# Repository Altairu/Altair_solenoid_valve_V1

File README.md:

# Altair_solenoid_valve_V1
Altair_solenoid_valve_V1

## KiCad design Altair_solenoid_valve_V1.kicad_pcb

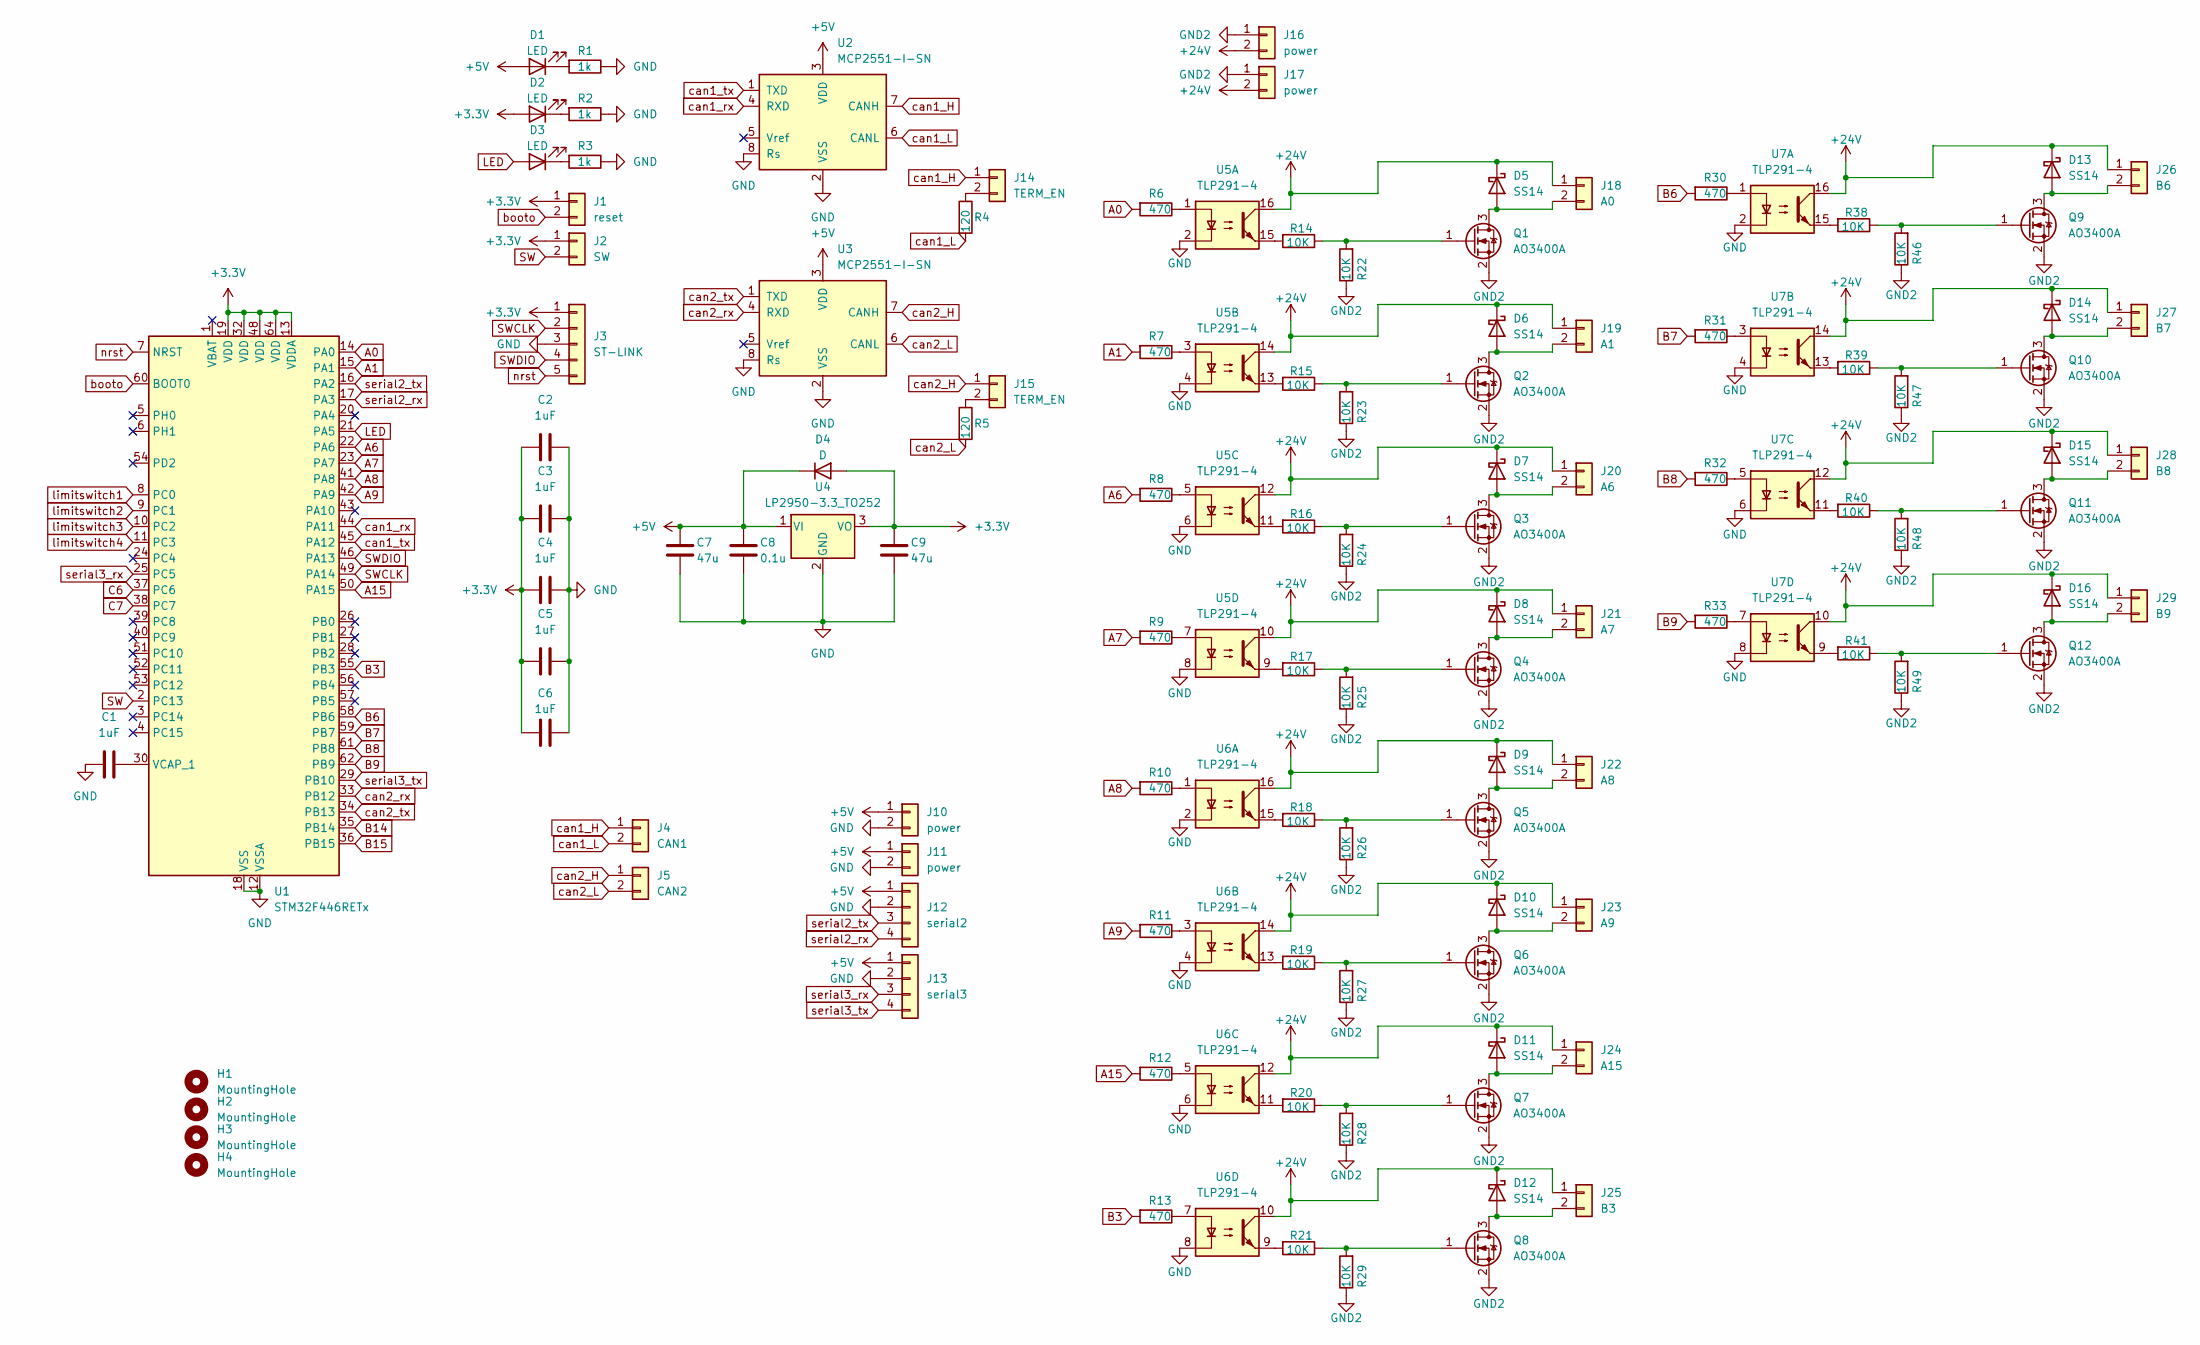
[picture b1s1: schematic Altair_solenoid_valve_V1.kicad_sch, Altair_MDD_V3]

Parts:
C1, C2, C3, C4, C5, C6: 1uF; C_0603_1608Metric
C7, C9: 47u; C_0603_1608Metric
C8: 0.1u; C_0603_1608Metric
D1, D2, D3: LED; LED_0603_1608Metric
D4: D; D_0603_1608Metric
D5, D6, D7, D8, D9, D10, D11, D12, D13, D14, D15, D16: SS14; D_SMA
H1, H2, H3, H4: MountingHole; MountingHole_3.2mm_M3_Pad_Via
J1: reset; PinSocket_1x02_P2.54mm_Vertical
J2: SW; PinSocket_1x02_P2.54mm_Vertical
J3: ST-LINK; PinSocket_1x05_P2.54mm_Vertical
J4: CAN1; JST_XA_S02B-XASK-1_1x02_P2.50mm_Horizontal
J5: CAN2; JST_XA_S02B-XASK-1_1x02_P2.50mm_Horizontal
J10, J11: power; JST_XA_S02B-XASK-1_1x02_P2.50mm_Horizontal
J12: serial2; JST_XA_B04B-XASK-1-A_1x04_P2.50mm_Vertical
J13: serial3; JST_XA_B04B-XASK-1-A_1x04_P2.50mm_Vertical
J14, J15: TERM_EN; PinSocket_1x02_P2.54mm_Vertical
J16, J17: power; AMASS_XT30PW-M_1x02_P2.50mm_Horizontal
J18: A0; AMASS_XT30U-F_1x02_P5.0mm_Vertical
J19: A1; AMASS_XT30U-F_1x02_P5.0mm_Vertical
J20: A6; AMASS_XT30U-F_1x02_P5.0mm_Vertical
J21: A7; AMASS_XT30U-F_1x02_P5.0mm_Vertical
J22: A8; AMASS_XT30U-F_1x02_P5.0mm_Vertical
J23: A9; AMASS_XT30U-F_1x02_P5.0mm_Vertical
J24: A15; AMASS_XT30U-F_1x02_P5.0mm_Vertical
J25: B3; AMASS_XT30U-F_1x02_P5.0mm_Vertical
J26: B6; AMASS_XT30U-F_1x02_P5.0mm_Vertical
J27: B7; AMASS_XT30U-F_1x02_P5.0mm_Vertical
J28: B8; AMASS_XT30U-F_1x02_P5.0mm_Vertical
J29: B9; AMASS_XT30U-F_1x02_P5.0mm_Vertical
Q1, Q2, Q3, Q4, Q5, Q6, Q7, Q8, Q9, Q10, Q11, Q12: AO3400A; SOT-23
R1, R2, R3: 1k; R_0603_1608Metric
R4, R5: 120; R_0603_1608Metric
R6, R7, R8, R9, R10, R11, R12, R13, R30, R31, R32, R33: 470; R_0603_1608Metric
R14, R15, R16, R17, R18, R19, R20, R21, R22, R23, R24, R25, R26, R27, R28, R29, R38, R39, R40, R41, R46, R47, R48, R49: 10K; R_0603_1608Metric
U1: STM32F446RETx; LQFP-64_10x10mm_P0.5mm
U2, U3: MCP2551-I-SN; SOIC-8_3.9x4.9mm_P1.27mm
U4: LP2950-3.3_TO252; TO-252-2
U5, U6, U7: TLP291-4; SOIC-16_4.55x10.3mm_P1.27mm

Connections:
+3.3V: C2.1, C3.1, C4.1, C5.1, C6.1, C9.1, D2.2 (A), D4.2 (A), J1.1, J2.1, J3.1, U1.13 (VDDA), U1.19 (VDD), U1.32 (VDD), U1.48 (VDD), U1.64 (VDD), U4.3 (VO)
+5V: C7.1, C8.1, D1.2 (A), D4.1 (K), J10.1, J11.1, J12.1, J13.1, U2.3 (VDD), U3.3 (VDD), U4.1 (VI)
+24V: D5.1 (K), D6.1 (K), D7.1 (K), D8.1 (K), D9.1 (K), D10.1 (K), D11.1 (K), D12.1 (K), D13.1 (K), D14.1 (K), D15.1 (K), D16.1 (K), J16.2, J17.2, J18.1, J19.1, J20.1, J21.1, J22.1, J23.1, J24.1, J25.1, J26.1, J27.1, J28.1, J29.1, U5.10, U5.12, U5.14, U5.16, U6.10, U6.12, U6.14, U6.16, U7.10, U7.12, U7.14, U7.16
A0: R6.2, U1.14 (PA0)
A1: R7.2, U1.15 (PA1)
A6: R8.2, U1.22 (PA6)
A7: R9.2, U1.23 (PA7)
A8: R10.2, U1.41 (PA8)
A9: R11.2, U1.42 (PA9)
A15: R12.2, U1.50 (PA15)
B3: R13.2, U1.55 (PB3)
B6: R30.2, U1.58 (PB6)
B7: R31.2, U1.59 (PB7)
B8: R32.2, U1.61 (PB8)
B9: R33.2, U1.62 (PB9)
B14: U1.35 (PB14)
B15: U1.36 (PB15)
C6: U1.37 (PC6)
C7: U1.38 (PC7)
GND: C1.1, C2.2, C3.2, C4.2, C5.2, C6.2, C7.2, C8.2, C9.2, J3.3, J10.2, J11.2, J12.2, J13.2, R1.1, R2.1, R3.1, U1.12 (VSSA), U1.18 (VSS), U1.31 (VSS), U1.47 (VSS), U1.63 (VSS), U2.2 (VSS), U2.8 (Rs), U3.2 (VSS), U3.8 (Rs), U4.2 (GND), U5.2, U5.4, U5.6, U5.8, U6.2, U6.4, U6.6, U6.8, U7.2, U7.4, U7.6, U7.8
GND2: J16.1, J17.1, Q1.2 (S), Q2.2 (S), Q3.2 (S), Q4.2 (S), Q5.2 (S), Q6.2 (S), Q7.2 (S), Q8.2 (S), Q9.2 (S), Q10.2 (S), Q11.2 (S), Q12.2 (S), R22.1, R23.1, R24.1, R25.1, R26.1, R27.1, R28.1, R29.1, R46.1, R47.1, R48.1, R49.1
LED: D3.2 (A), U1.21 (PA5)
unnamed: D1.1 (K), R1.2
unnamed: D2.1 (K), R2.2
unnamed: D3.1 (K), R3.2
unnamed: D5.2 (A), J18.2, Q1.3 (D)
unnamed: D6.2 (A), J19.2, Q2.3 (D)
unnamed: D7.2 (A), J20.2, Q3.3 (D)
unnamed: D8.2 (A), J21.2, Q4.3 (D)
unnamed: D9.2 (A), J22.2, Q5.3 (D)
unnamed: D10.2 (A), J23.2, Q6.3 (D)
unnamed: D11.2 (A), J24.2, Q7.3 (D)
unnamed: D12.2 (A), J25.2, Q8.3 (D)
unnamed: D13.2 (A), J26.2, Q9.3 (D)
unnamed: D14.2 (A), J27.2, Q10.3 (D)
unnamed: D15.2 (A), J28.2, Q11.3 (D)
unnamed: D16.2 (A), J29.2, Q12.3 (D)
unnamed: J14.2, R4.1
unnamed: J15.2, R5.1
unnamed: Q1.1 (G), R14.1, R22.2
unnamed: Q2.1 (G), R15.1, R23.2
unnamed: Q3.1 (G), R16.1, R24.2
unnamed: Q4.1 (G), R17.1, R25.2
unnamed: Q5.1 (G), R18.1, R26.2
unnamed: Q6.1 (G), R19.1, R27.2
unnamed: Q7.1 (G), R20.1, R28.2
unnamed: Q8.1 (G), R21.1, R29.2
unnamed: Q9.1 (G), R38.1, R46.2
unnamed: Q10.1 (G), R39.1, R47.2
unnamed: Q11.1 (G), R40.1, R48.2
unnamed: Q12.1 (G), R41.1, R49.2
unnamed: R6.1, U5.1
unnamed: R7.1, U5.3
unnamed: R8.1, U5.5
unnamed: R9.1, U5.7
unnamed: R10.1, U6.1
unnamed: R11.1, U6.3
unnamed: R12.1, U6.5
unnamed: R13.1, U6.7
unnamed: R14.2, U5.15
unnamed: R15.2, U5.13
unnamed: R16.2, U5.11
unnamed: R17.2, U5.9
unnamed: R18.2, U6.15
unnamed: R19.2, U6.13
unnamed: R20.2, U6.11
unnamed: R21.2, U6.9
unnamed: R30.1, U7.1
unnamed: R31.1, U7.3
unnamed: R32.1, U7.5
unnamed: R33.1, U7.7
unnamed: R38.2, U7.15
unnamed: R39.2, U7.13
unnamed: R40.2, U7.11
unnamed: R41.2, U7.9
unnamed: C1.2, U1.30 (VCAP_1)
SW: J2.2, U1.2 (PC13)
SWCLK: J3.2, U1.49 (PA14)
SWDIO: J3.4, U1.46 (PA13)
booto: J1.2, U1.60 (BOOT0)
can1_H: J4.1, J14.1, U2.7 (CANH)
can1_L: J4.2, R4.2, U2.6 (CANL)
can1_rx: U1.44 (PA11), U2.4 (RXD)
can1_tx: U1.45 (PA12), U2.1 (TXD)
can2_H: J5.1, J15.1, U3.7 (CANH)
can2_L: J5.2, R5.2, U3.6 (CANL)
can2_rx: U1.33 (PB12), U3.4 (RXD)
can2_tx: U1.34 (PB13), U3.1 (TXD)
limitswitch1: U1.8 (PC0)
limitswitch2: U1.9 (PC1)
limitswitch3: U1.10 (PC2)
limitswitch4: U1.11 (PC3)
nrst: J3.5, U1.7 (NRST)
serial2_rx: J12.4, U1.17 (PA3)
serial2_tx: J12.3, U1.16 (PA2)
serial3_rx: J13.3, U1.25 (PC5)
serial3_tx: J13.4, U1.29 (PB10)

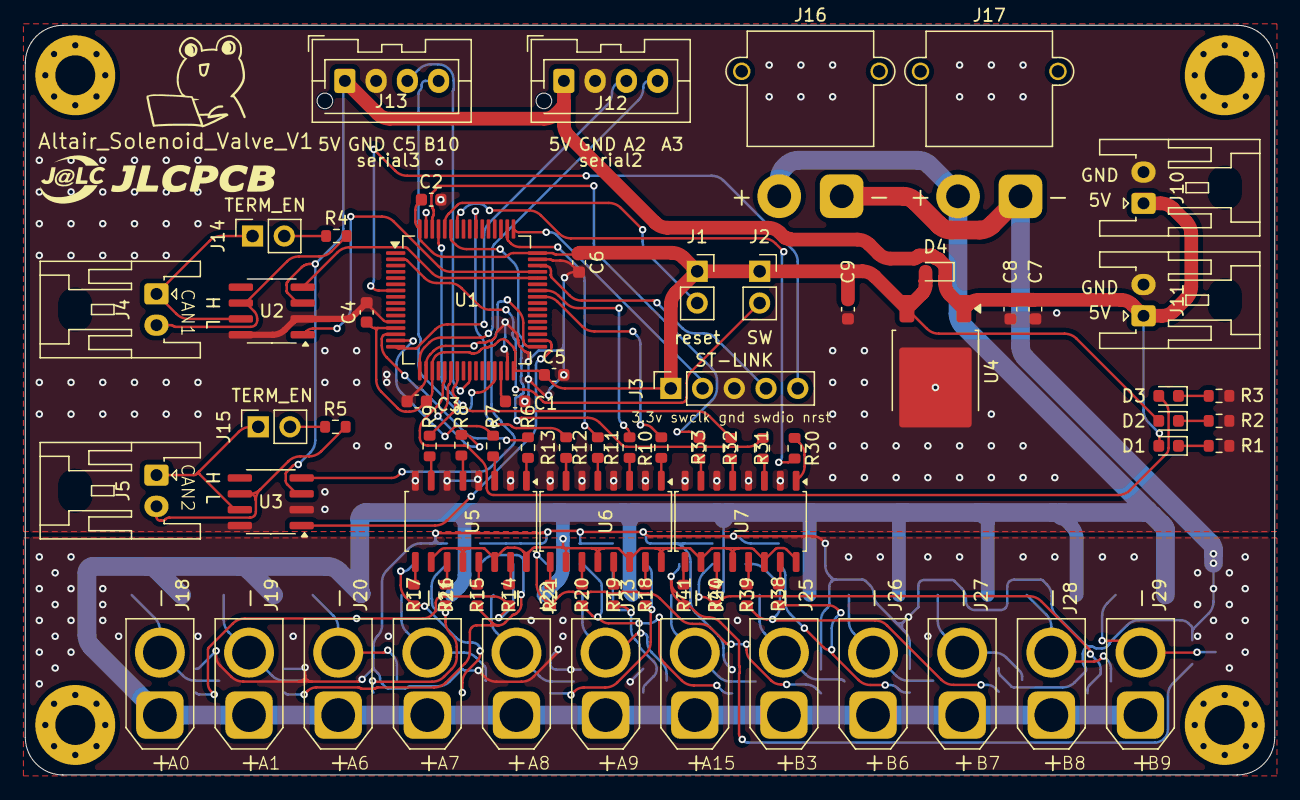
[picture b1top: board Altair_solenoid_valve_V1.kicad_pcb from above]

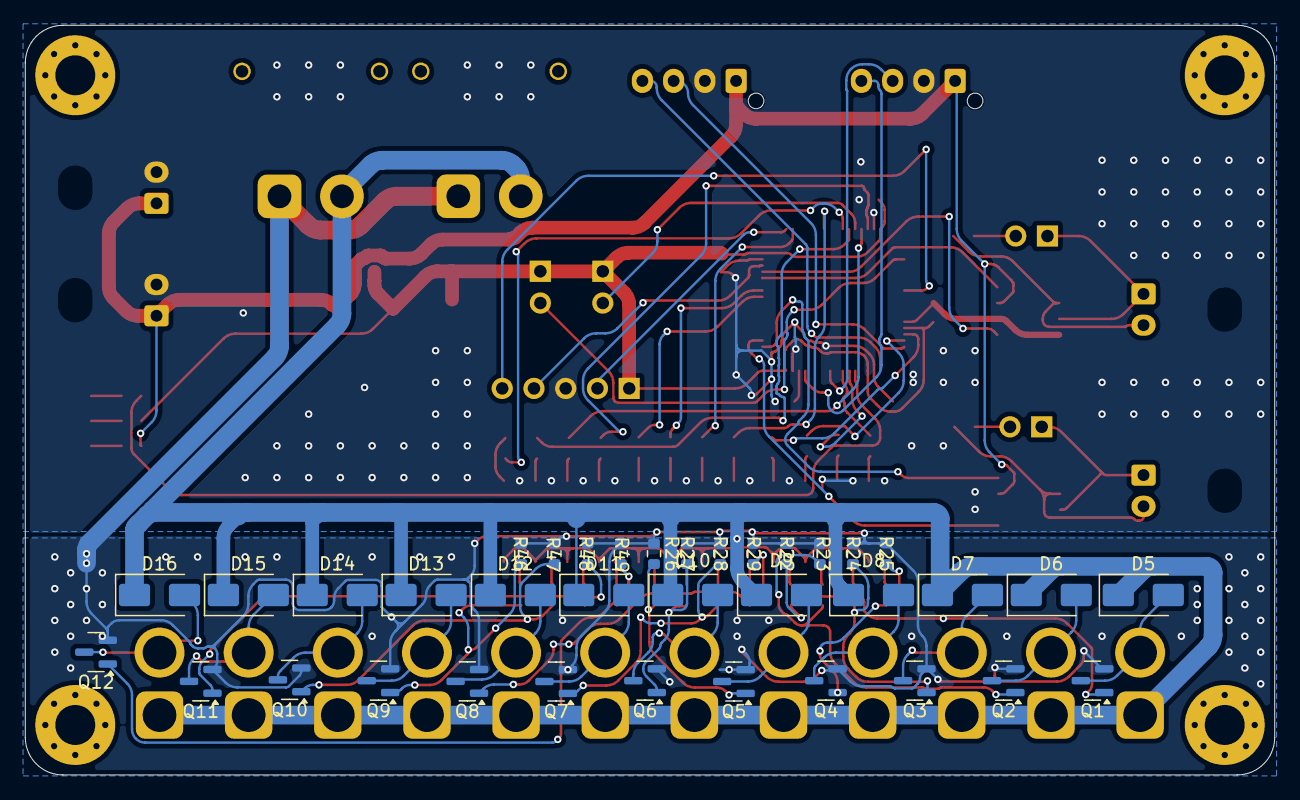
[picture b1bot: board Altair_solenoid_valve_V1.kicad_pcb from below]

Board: 2 copper layers, 100.0 x 60.0 mm, 114 parts (36 on the bottom side), 89 nets.

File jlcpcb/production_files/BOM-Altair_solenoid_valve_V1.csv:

Comment,Designator,Footprint,LCSC,Quantity
0.1u,C8,C_0603_1608Metric,C125205,1
10K,"R14,R15,R16,R17,R18,R19,R20,R21,R22,R23,R24,R25,R26,R27,R28,R29,R38,R39,R40,R41,R46,R47,R48,R49",R_0603_1608Metric,C15401,24
120,"R4,R5",R_0603_1608Metric,C14709,2
1k,"R1,R2,R3",R_0603_1608Metric,C78748,3
1uF,"C1,C2,C3,C4,C5,C6",C_0603_1608Metric,C1592,6
470,"R10,R11,R12,R13,R30,R31,R32,R33,R6,R7,R8,R9",R_0603_1608Metric,C23179,12
47u,"C7,C9",C_0603_1608Metric,C140782,2
AO3400A,"Q1,Q10,Q11,Q12,Q2,Q3,Q4,Q5,Q6,Q7,Q8,Q9",SOT-23,C347475,12
D,D4,D_0603_1608Metric,C3758192,1
LED,"D1,D2,D3",LED_0603_1608Metric,C2290,3
LP2950-3.3_TO252,U4,TO-252-2,C129994,1
MCP2551-I-SN,"U2,U3",SOIC-8_3.9x4.9mm_P1.27mm,C7376,2
SS14,"D10,D11,D12,D13,D14,D15,D16,D5,D6,D7,D8,D9",D_SMA,C2480,12
STM32F446RETx,U1,LQFP-64_10x10mm_P0.5mm,C69336,1
TLP291-4,"U5,U6,U7",SOIC-16_4.55x10.3mm_P1.27mm,C60900,3
